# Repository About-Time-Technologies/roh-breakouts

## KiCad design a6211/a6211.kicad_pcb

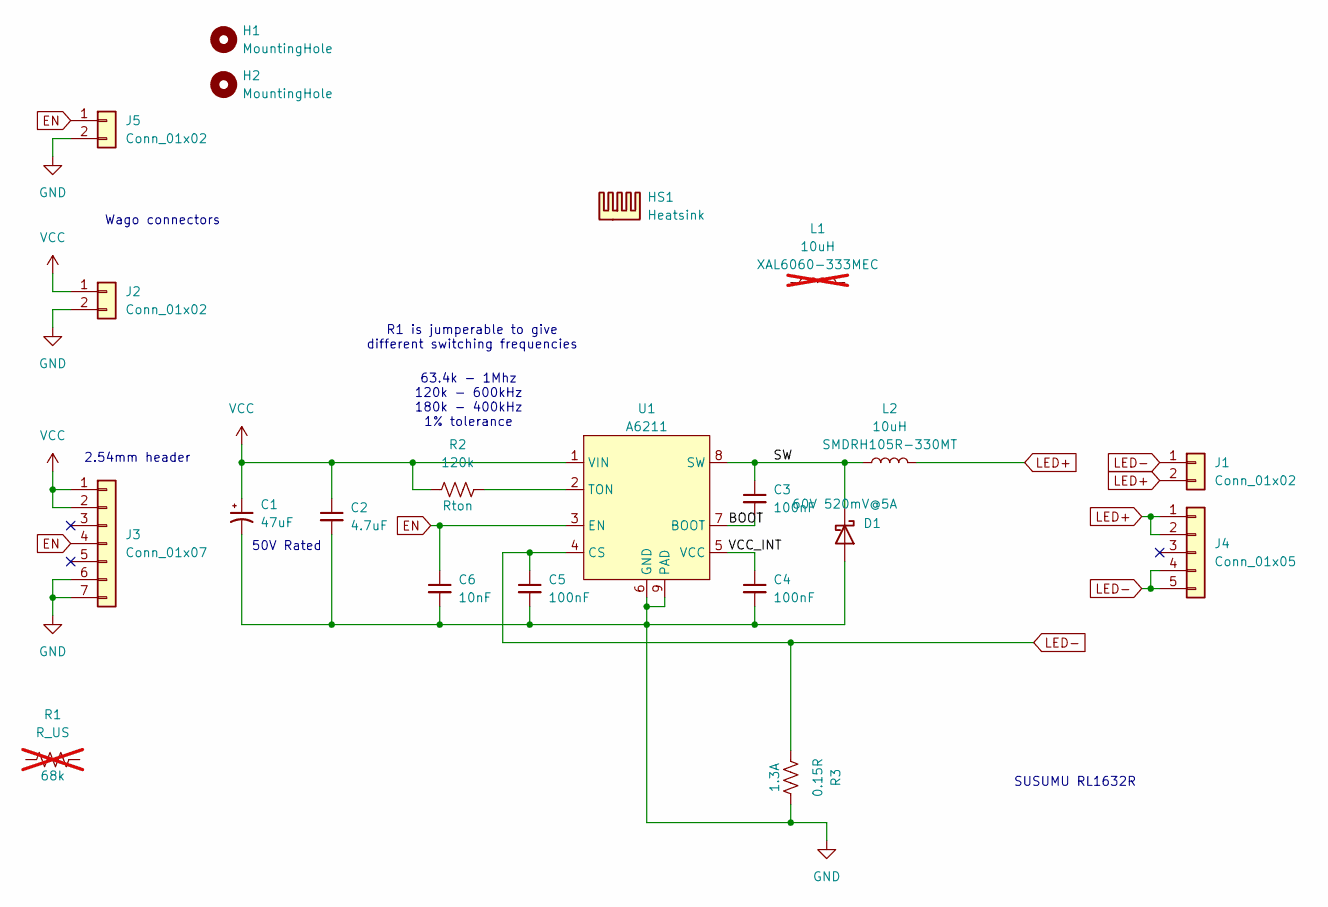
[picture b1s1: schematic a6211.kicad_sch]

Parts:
C1: 47uF; CP_Elec_8x10; LCSC C40078
C2: 4.7uF; C_1206_3216Metric; LCSC C29823
C3, C4, C5: 100nF; C_0603_1608Metric; LCSC C14663
C6: 10nF; C_0603_1608Metric; LCSC C57112
D1: D_Schottky; D_SMC; LCSC C7436542
H1, H2: MountingHole; MountingHole_3.2mm_M3
HS1: Heatsink; HSB02-101007
J1, J2: Conn_01x02; 2060-452-998-404 Wago
J3: Conn_01x07; PinHeader_1x07_P2.54mm_Vertical
J4: Conn_01x05; PinHeader_1x05_P2.54mm_Vertical
J5: Conn_01x02; PinHeader_1x02_P2.54mm_Vertical
L1: 10uH; L_Coilcraft_XAL6060-XXX; LCSC C5119929; not fitted
L2: 10uH; L_10.4x10.4_H4.8; LCSC C9186
R1: R_US; R_0603_1608Metric_Pad0.98x0.95mm_HandSolder; LCSC C23231; not fitted
R2: 120k; R_0603_1608Metric_Pad0.98x0.95mm_HandSolder; LCSC C25808
R3: 0.15R; R_1206_3216Metric; LCSC C2683383
U1: A6211; SOIC-8-1EP_3.9x4.9mm_P1.27mm_EP2.41x3.3mm_ThermalVias; LCSC C150827

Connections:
/BOOT: C3.2, U1.7 (BOOT)
/SW: C3.1, D1.1 (K), L2.1, U1.8 (SW)
/VCC_INT: C4.1, U1.5 (VCC)
EN: C6.1, J3.4, J5.1, U1.3 (EN)
GND: C1.2, C2.2, C4.2, C5.2, C6.2, D1.2 (A), J2.2, J3.6, J3.7, J5.2, R3.2, U1.6 (GND), U1.9 (PAD)
LED+: J1.2, J4.1, J4.2, L2.2
LED-: C5.1, J1.1, J4.4, J4.5, R3.1, U1.4 (CS)
unnamed: R2.2, U1.2 (TON)
VCC: C1.1, C2.1, J2.1, J3.1, J3.2, R2.1, U1.1 (VIN)

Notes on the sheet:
63.4k - 1Mhz 120k - 600kHz 180k - 400kHz 1% tolerance
SUSUMU RL1632R
2.54mm header
R1 is jumperable to give different switching frequencies
Wago connectors
50V Rated

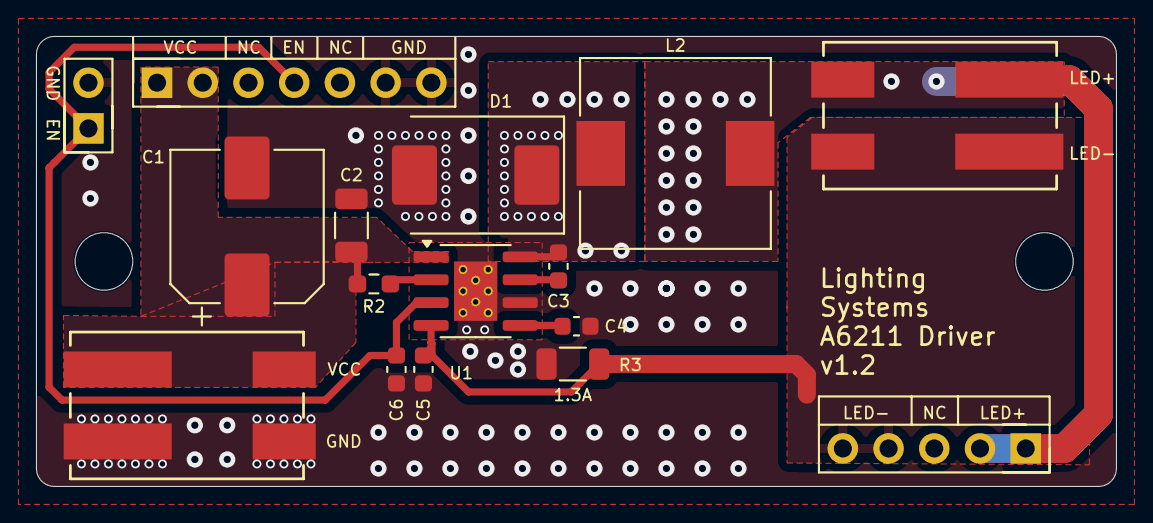
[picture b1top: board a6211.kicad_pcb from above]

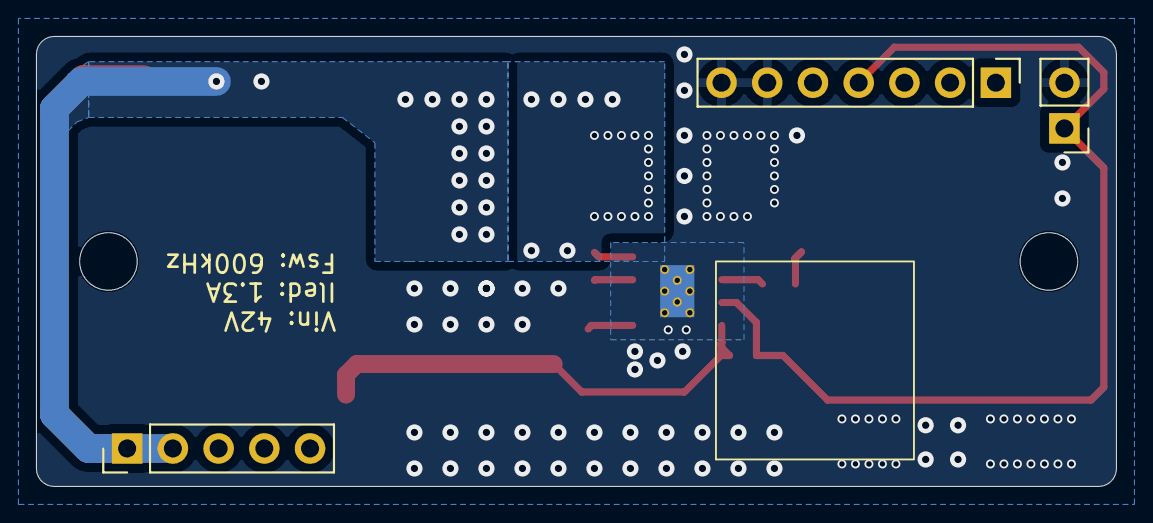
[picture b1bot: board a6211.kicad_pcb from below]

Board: 2 copper layers, 60.0 x 25.0 mm, 19 parts (4 on the bottom side), 9 nets.

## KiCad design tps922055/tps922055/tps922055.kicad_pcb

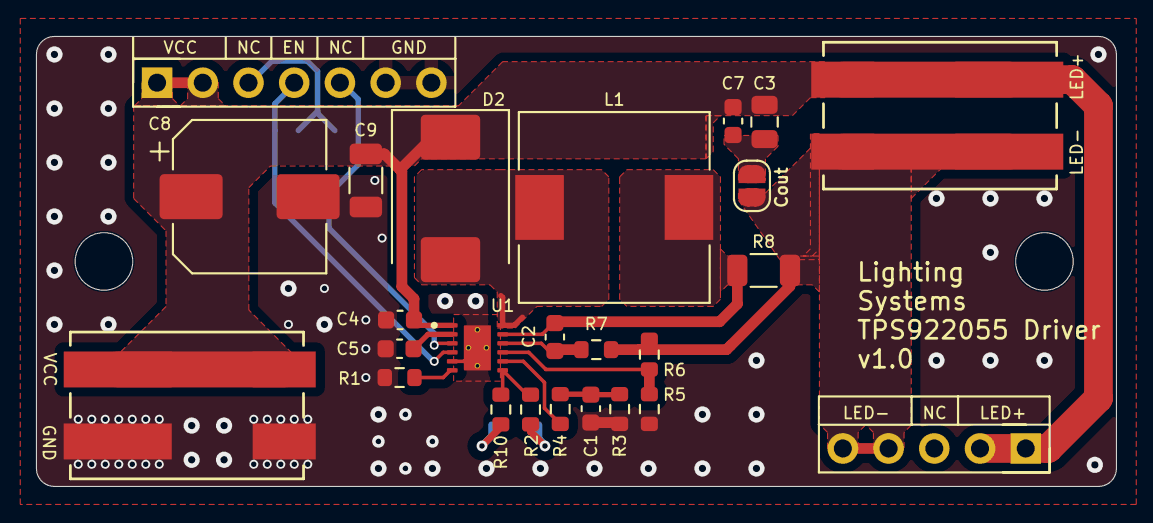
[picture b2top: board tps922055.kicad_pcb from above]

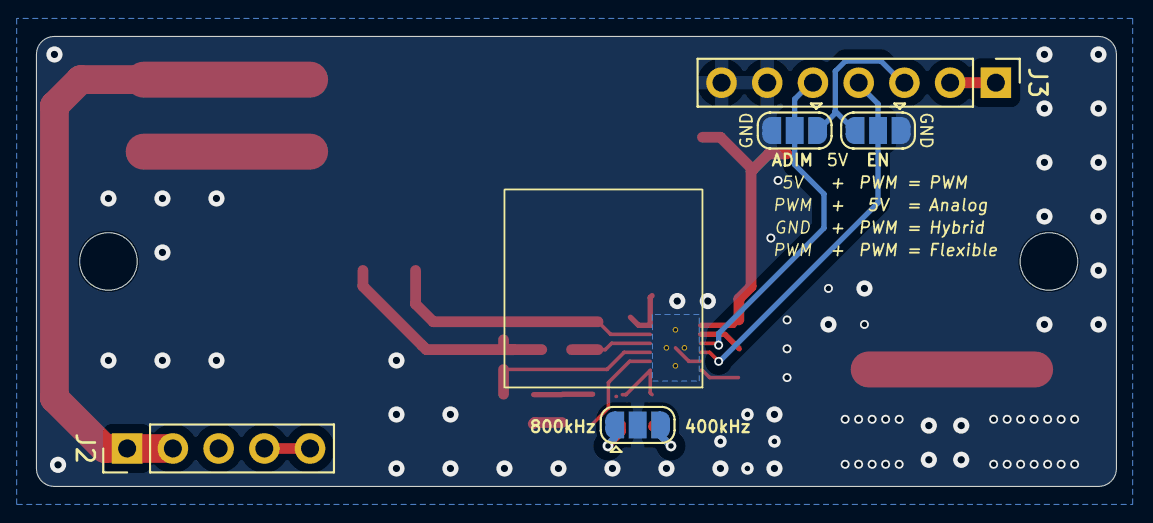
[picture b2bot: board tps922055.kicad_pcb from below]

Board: 2 copper layers, 60.0 x 25.0 mm, 31 parts (6 on the bottom side), 18 nets.

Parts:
C1, C2: 1nF; C_0603_1608Metric
C3: 1uF; C_0805_2012Metric
C4, C7: 100nF; C_0603_1608Metric
C5: 1uF; C_0603_1608Metric
C8: 47uF; CP_Elec_8x10
C9: 4.7uF; C_1206_3216Metric
D2: D_Schottky; D_SMC
H1, H2: MountingHole; MountingHole_3.2mm_M3
HS1: Heatsink; HSB02-101007
J1, J4: Conn_01x02; 2060-452-998-404 Wago
J2: Conn_01x05; PinHeader_1x05_P2.54mm_Vertical
J3: Conn_01x07; PinHeader_1x07_P2.54mm_Vertical
JP1, JP2, JP5: Jumper_3_Open; SolderJumper-3_P1.3mm_Open_RoundedPad1.0x1.5mm
JP3: Jumper_2_Open; SolderJumper-2_P1.3mm_Open_RoundedPad1.0x1.5mm
L1: 22uH; L_10.4x10.4_H4.8
R1, R2: 27k; R_0603_1608Metric
R3, R5, R6: 1M0; R_0603_1608Metric
R4, R7: 100R; R_0603_1608Metric
R8: 0.15R; R_1206_3216Metric
R10: 56k; R_0603_1608Metric
U1: TPS922052DRRR; SON50P300X300X100-13N

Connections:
5V: J3.3, JP1.3 (B), JP2.1 (A)
/COMP: R4.1, U1.8 (COMP)
/COMP2: C1.1, R3.1, R4.2
/CSN: C2.1, L1.2, R8.1, U1.11 (CSN)
/CSP: C2.2, R7.1, U1.10 (CSP)
/FSET: R2.1, R10.1, U1.7 (FSET)
/OUTCAP: C3.2, C7.2, JP3.2 (B)
/SW: D2.2 (A), L1.1, U1.12 (SW)
/TEMP: R1.1, U1.6 (TEMP)
/UVP: R5.1, R6.2, U1.9 (UVP)
/VCC: C5.2, U1.2 (VCC)
ADIM: J3.5, JP2.2 (C), U1.3 (ADIM/HD)
EN: J3.4, JP1.2 (C), U1.4 (EN/PWM)
GND: C1.2, C4.2, C5.1, C8.2, C9.2, J3.6, J3.7, J4.2, JP1.1 (A), JP2.3 (B), JP5.2 (C), R1.2, R3.2, R5.2, U1.5 (FAULT), U1.13 (GND), U1.14 (PAD), U1.15 (PAD), U1.16 (PAD), U1.17 (PAD)
LED+: C3.1, C4.1, C7.1, C8.1, C9.1, D2.1 (K), J1.2, J2.1, J2.2, J3.1, J3.2, J4.1, U1.1 (VIN)
LED-: J1.1, J2.4, J2.5, JP3.1 (A), R6.1, R7.2, R8.2
unnamed: JP5.1 (A), R2.2
unnamed: JP5.3 (B), R10.2

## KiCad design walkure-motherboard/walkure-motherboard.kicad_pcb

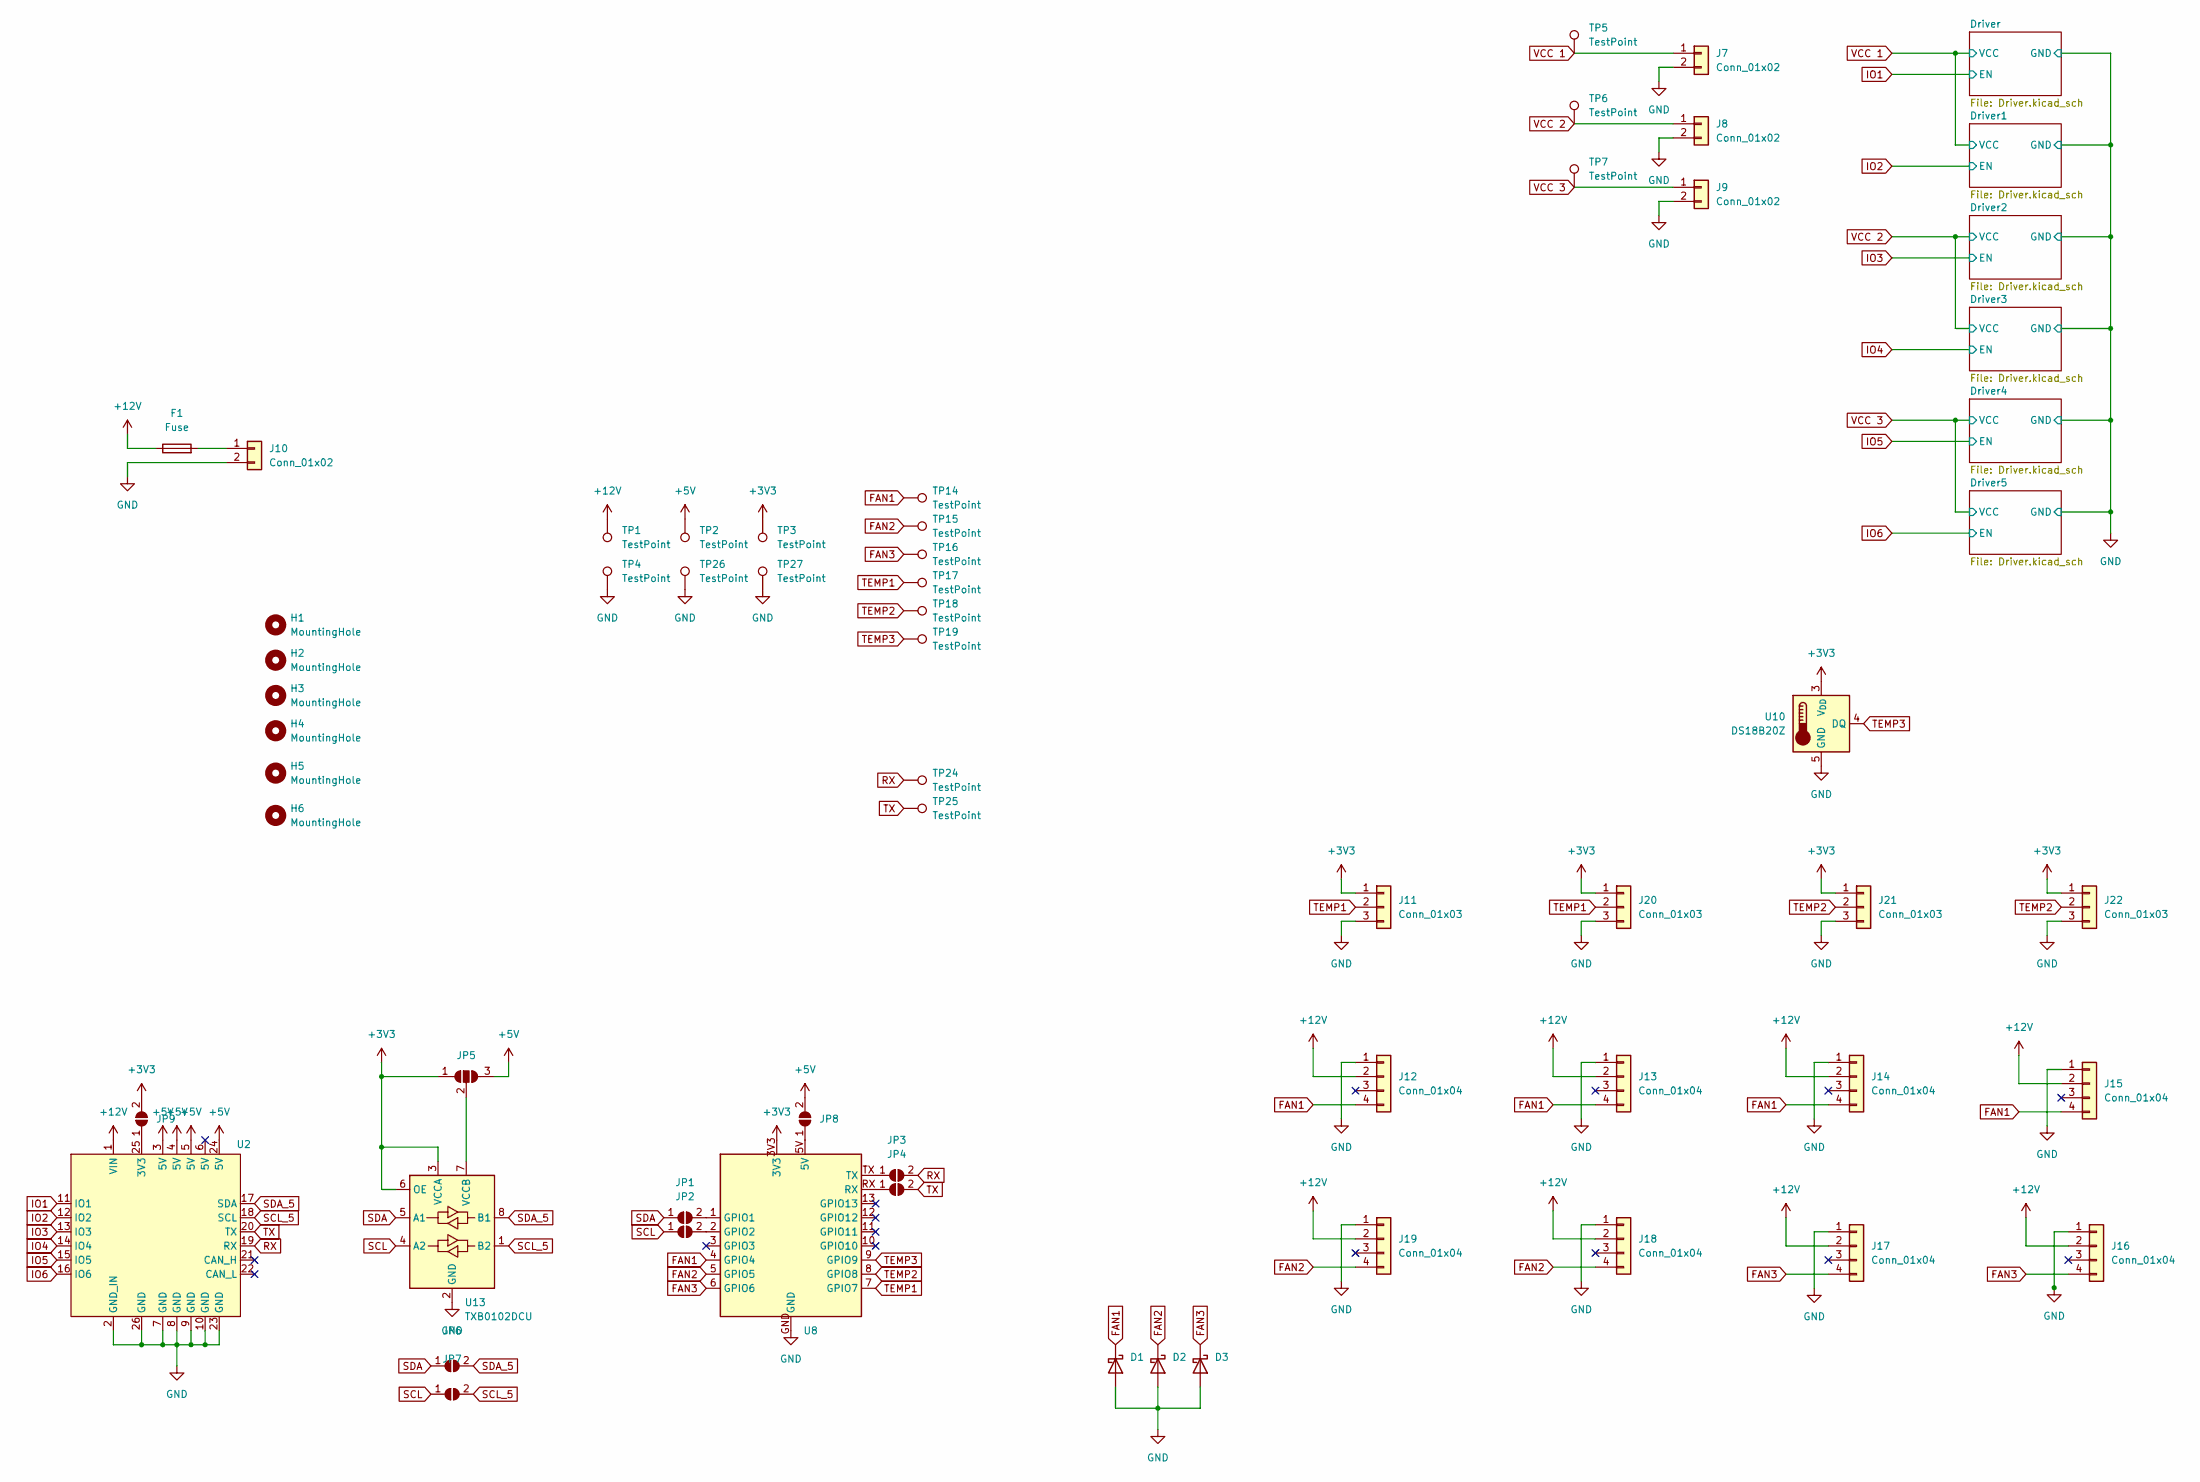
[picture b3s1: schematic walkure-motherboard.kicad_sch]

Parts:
D1, D2, D3: D_Schottky; D_DO-41_SOD81_P5.08mm_Vertical_AnodeUp
F1: Fuse; Keystone 4628
H1, H2, H3, H4, H5, H6: MountingHole; MountingHole_3.2mm_M3_ISO14580
J7, J8, J9, J10: Conn_01x02; 2060-452-998-404 Wago
J11, J20, J21, J22: Conn_01x03; PinHeader_1x03_P2.54mm_Vertical
J12, J13, J14, J15, J16, J17, J18, J19: Conn_01x04; PinHeader_1x04_P2.54mm_Vertical
JP1, JP2, JP3, JP4, JP6, JP7, JP8, JP9: SolderJumper_2_Open; SolderJumper-2_P1.3mm_Open_RoundedPad1.0x1.5mm
JP5: SolderJumper_3_Open; SolderJumper-3_P1.3mm_Open_RoundedPad1.0x1.5mm
TP1, TP2, TP3, TP4, TP5, TP6, TP7, TP14, TP15, TP16, TP17, TP18, TP19, TP24, TP25, TP26, TP27: TestPoint; TestPoint_Pad_D2.0mm
U2: MHCI-DMX
U8: ESP-32-S3-Zero - PTH
U10: DS18B20Z; SOIC-8_3.9x4.9mm_P1.27mm
U13: TXB0102DCU; VSSOP-8_2.3x2mm_P0.5mm; LCSC C60709

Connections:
+3V3: J11.1, J20.1, J21.1, J22.1, JP5.1 (A), JP9.2 (B), TP3.1, U8.3V3, U10.3 (V_{DD}), U13.3 (VCCA), U13.6 (OE)
+5V: JP5.3 (B), JP8.2 (B), TP2.1, U2.3 (5V), U2.4 (5V), U2.5 (5V), U2.24 (5V)
+12V: F1.1, J12.2, J13.2, J14.2, J15.2, J16.2, J17.2, J18.2, J19.2, TP1.1, U2.1 (VIN)
FAN1: D1.1 (K), J12.4, J13.4, J14.4, J15.4, TP14.1, U8.4 (GPIO4)
FAN2: D2.1 (K), J18.4, J19.4, TP15.1, U8.5 (GPIO5)
FAN3: D3.1 (K), J16.4, J17.4, TP16.1, U8.6 (GPIO6)
GND: D1.2 (A), D2.2 (A), D3.2 (A), J7.2, J8.2, J9.2, J10.2, J11.3, J12.1, J13.1, J14.1, J15.1, J16.1, J17.1, J18.1, J19.1, J20.3, J21.3, J22.3, TP4.1, TP26.1, TP27.1, U2.2 (GND_IN), U2.7 (GND), U2.8 (GND), U2.9 (GND), U2.10 (GND), U2.23 (GND), U2.26 (GND), U8.GND, U10.5 (GND), U13.2 (GND); also elsewhere on the board
IO1: U2.11 (IO1); also elsewhere on the board
IO2: U2.12 (IO2); also elsewhere on the board
IO3: U2.13 (IO3); also elsewhere on the board
IO4: U2.14 (IO4); also elsewhere on the board
IO5: U2.15 (IO5); also elsewhere on the board
IO6: U2.16 (IO6); also elsewhere on the board
unnamed: F1.2, J10.1
unnamed: JP1.2 (B), U8.1 (GPIO1)
unnamed: JP2.2 (B), U8.2 (GPIO2)
unnamed: JP3.1 (A), U8.TX
unnamed: JP4.1 (A), U8.RX
unnamed: JP5.2 (C), U13.7 (VCCB)
unnamed: JP8.1 (A), U8.5V
unnamed: JP9.1 (A), U2.25 (3V3)
RX: JP3.2 (B), TP24.1, U2.19 (RX)
SCL: JP2.1 (A), JP7.1 (A), U13.4 (A2)
SCL_5: JP7.2 (B), U2.18 (SCL), U13.1 (B2)
SDA: JP1.1 (A), JP6.1 (A), U13.5 (A1)
SDA_5: JP6.2 (B), U2.17 (SDA), U13.8 (B1)
TEMP1: J11.2, J20.2, TP17.1, U8.7 (GPIO7)
TEMP2: J21.2, J22.2, TP18.1, U8.8 (GPIO8)
TEMP3: TP19.1, U8.9 (GPIO9), U10.4 (DQ)
TX: JP4.2 (B), TP25.1, U2.20 (TX)
VCC 1: J7.1, TP5.1; also elsewhere on the board
VCC 2: J8.1, TP6.1; also elsewhere on the board
VCC 3: J9.1, TP7.1; also elsewhere on the board

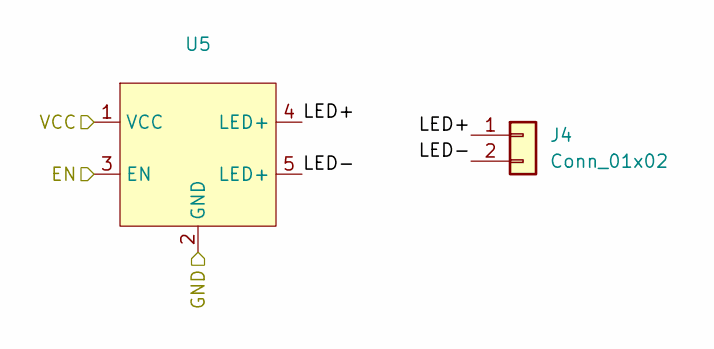
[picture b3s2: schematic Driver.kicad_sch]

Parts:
J4: Conn_01x02; 2060-452-998-404 Wago
U5: MHCI-A6211

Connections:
/Driver3/LED+: J4.1, U5.4 (LED+)
/Driver3/LED-: J4.2, U5.5 (LED+)
GND: U5.2 (GND); also elsewhere on the board
IO4: U5.3 (EN); also elsewhere on the board
VCC 2: U5.1 (VCC); also elsewhere on the board

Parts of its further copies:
J1, J2, J3, J5, J6: Conn_01x02; 2060-452-998-404 Wago
U1, U3, U4, U6, U7: MHCI-A6211

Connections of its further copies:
/Driver1/LED+: J1.1, U3.4 (LED+)
/Driver1/LED-: J1.2, U3.5 (LED+)
/Driver2/LED+: J3.1, U4.4 (LED+)
/Driver2/LED-: J3.2, U4.5 (LED+)
/Driver4/LED+: J5.1, U6.4 (LED+)
/Driver4/LED-: J5.2, U6.5 (LED+)
/Driver5/LED+: J6.1, U7.4 (LED+)
/Driver5/LED-: J6.2, U7.5 (LED+)
/Driver/LED+: J2.1, U1.4 (LED+)
/Driver/LED-: J2.2, U1.5 (LED+)
GND: U1.2 (GND), U3.2 (GND), U4.2 (GND), U6.2 (GND), U7.2 (GND); also elsewhere on the board
IO1: U1.3 (EN); also elsewhere on the board
IO2: U3.3 (EN); also elsewhere on the board
IO3: U4.3 (EN); also elsewhere on the board
IO5: U6.3 (EN); also elsewhere on the board
IO6: U7.3 (EN); also elsewhere on the board
VCC 1: U1.1 (VCC), U3.1 (VCC); also elsewhere on the board
VCC 2: U4.1 (VCC); also elsewhere on the board
VCC 3: U6.1 (VCC), U7.1 (VCC); also elsewhere on the board

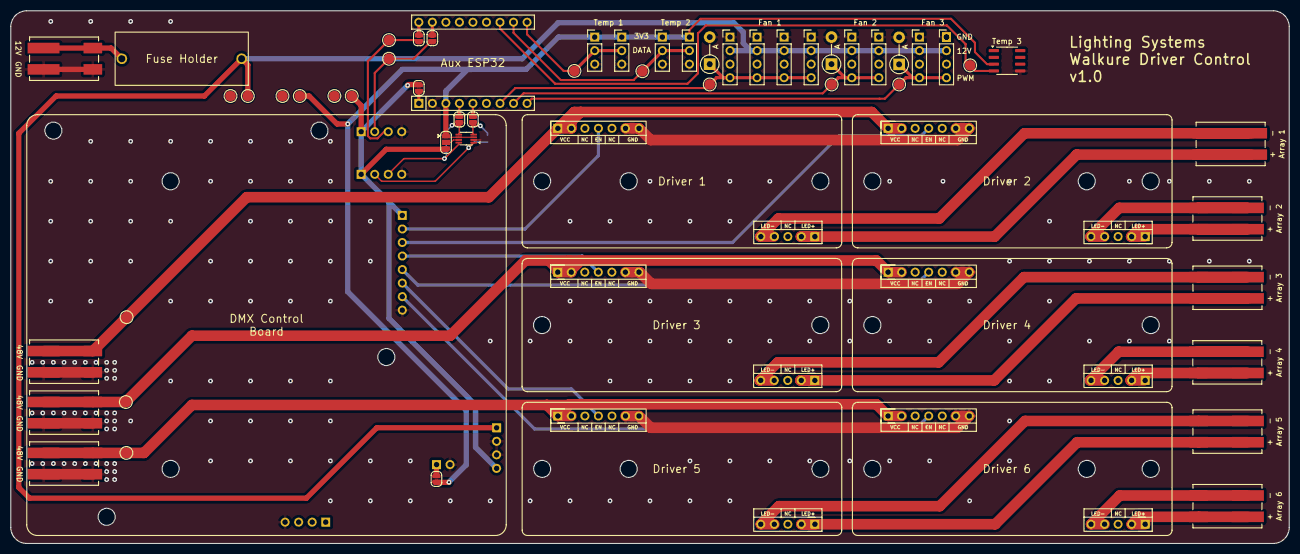
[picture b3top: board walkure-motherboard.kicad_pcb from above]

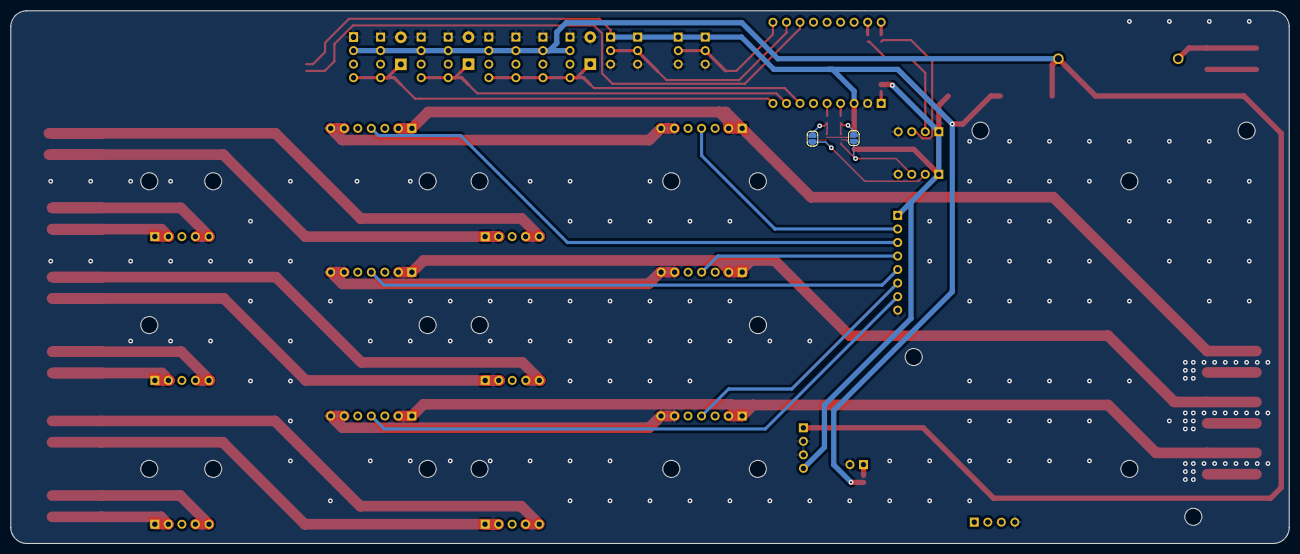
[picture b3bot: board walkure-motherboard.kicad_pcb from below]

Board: 2 copper layers, 240.0 x 100.0 mm, 68 parts (2 on the bottom side), 45 nets.

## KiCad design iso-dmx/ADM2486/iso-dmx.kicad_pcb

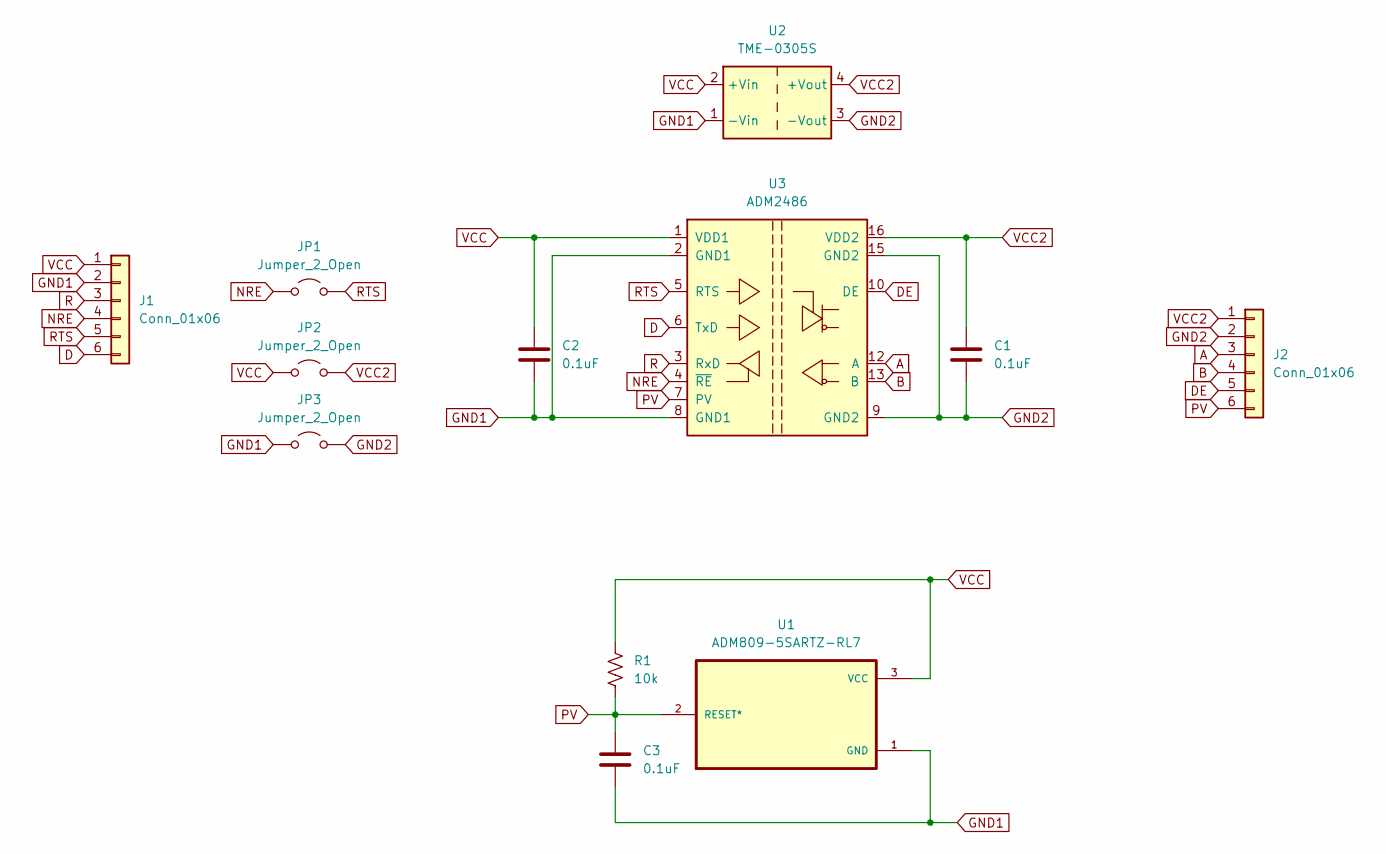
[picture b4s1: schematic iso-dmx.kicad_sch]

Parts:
C1, C2, C3: 0.1uF; C_1206_3216Metric_Pad1.33x1.80mm_HandSolder
J1, J2: Conn_01x06; PinHeader_1x06_P2.54mm_Vertical
JP1, JP2, JP3: Jumper_2_Open; SolderJumper-2_P1.3mm_Open_Pad1.0x1.5mm
R1: 10k; R_1206_3216Metric_Pad1.30x1.75mm_HandSolder
U1: ADM809-5SARTZ-RL7; SOT96P237X112-3N
U2: TME-0305S; Converter_DCDC_TRACO_TME_03xxS_05xxS_12xxS_Single_THT
U3: ADM2486; SOIC-16W_7.5x10.3mm_P1.27mm

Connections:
A: J2.3, U3.12 (A)
B: J2.4, U3.13 (B)
D: J1.6, U3.6 (TxD)
DE: J2.5, U3.10 (DE)
GND1: C2.2, C3.2, J1.2, JP3.1 (A), U1.1 (GND), U2.1 (-Vin), U3.2 (GND1), U3.8 (GND1)
GND2: C1.2, J2.2, JP3.2 (B), U2.3 (-Vout), U3.9 (GND2), U3.15 (GND2)
NRE: J1.4, JP1.1 (A), U3.4 (~RE)
PV: C3.1, J2.6, R1.2, U1.2 (RESET*), U3.7 (PV)
R: J1.3, U3.3 (RxD)
RTS: J1.5, JP1.2 (B), U3.5 (RTS)
VCC: C2.1, J1.1, JP2.1 (A), R1.1, U1.3 (VCC), U2.2 (+Vin), U3.1 (VDD1)
VCC2: C1.1, J2.1, JP2.2 (B), U2.4 (+Vout), U3.16 (VDD2)

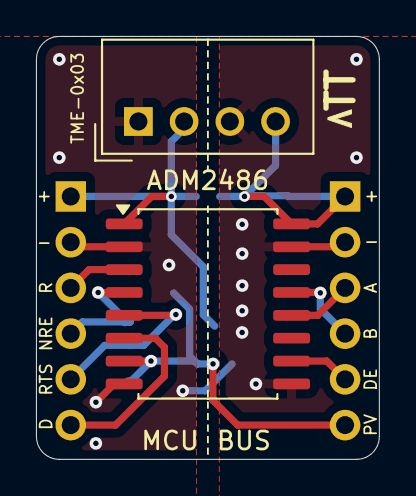
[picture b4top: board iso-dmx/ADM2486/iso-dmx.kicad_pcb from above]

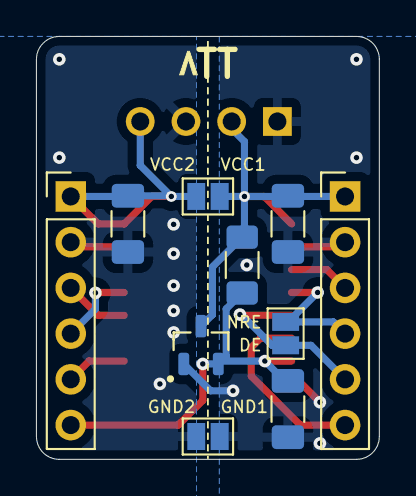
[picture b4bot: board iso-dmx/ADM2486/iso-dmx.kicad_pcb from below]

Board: 2 copper layers, 19.0 x 23.5 mm, 12 parts (10 on the bottom side), 12 nets.

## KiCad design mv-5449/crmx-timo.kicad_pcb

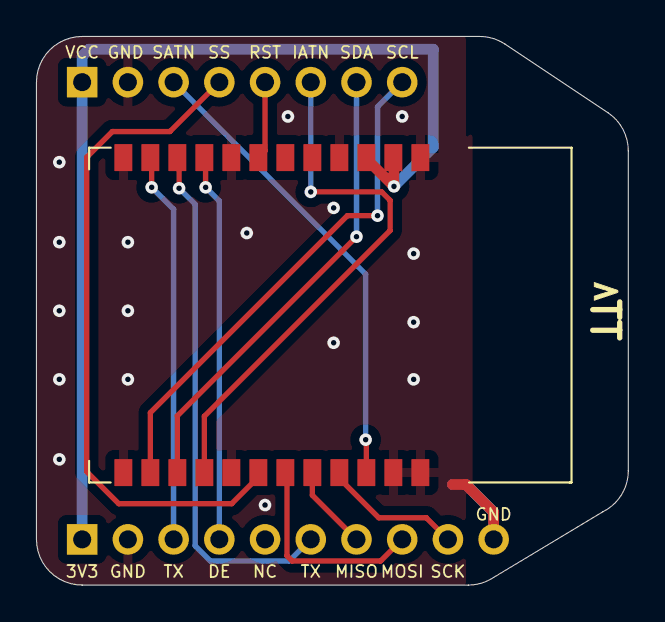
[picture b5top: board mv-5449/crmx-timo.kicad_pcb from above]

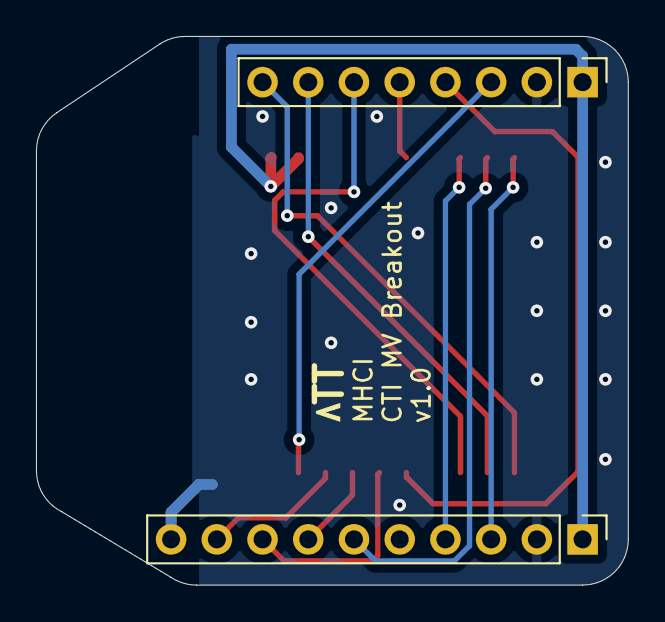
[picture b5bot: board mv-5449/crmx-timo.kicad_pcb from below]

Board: 2 copper layers, 32.9 x 30.5 mm, 3 parts (2 on the bottom side), 14 nets.

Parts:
J1: Conn_01x10; PinHeader_1x10_P2.54mm_Vertical
J2: Conn_01x08; PinHeader_1x08_P2.54mm_Vertical
U2: CTI-5994

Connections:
CTI_RESET: J2.5, U2.7 (nRESET)
DMX_DE: J1.4, U2.9 (UART_TXE)
DMX_RX: J1.6, U2.10 (UART_RX)
DMX_TX: J1.3, U2.11 (UART_TX)
GND: J1.2, J1.10, J2.2, U2.1 (GND), U2.4 (GND), U2.8 (GND), U2.12 (GND), U2.13 (GND), U2.17 (GND), U2.23 (GND), U2.24 (GND)
I2C_SCL: J2.8, U2.14 (I2C_SCL)
I2C_SDA: J2.7, U2.15 (I2C_SDA)
I2C_nATTN: J2.6, U2.16 (I2C_nATTN)
SPI_MISO: J1.7, U2.20 (SPI_MISO)
SPI_MOSI: J1.8, U2.19 (SPI_MOSI)
SPI_SCK: J1.9, U2.21 (SPI_CLK)
SPI_nATTN: J2.3, U2.22 (SPI_nATTN)
SPI_nSS: J2.4, U2.18 (SPI_nSS)
VCC: J1.1, J2.1, U2.2 (VCC), U2.3 (VCC)

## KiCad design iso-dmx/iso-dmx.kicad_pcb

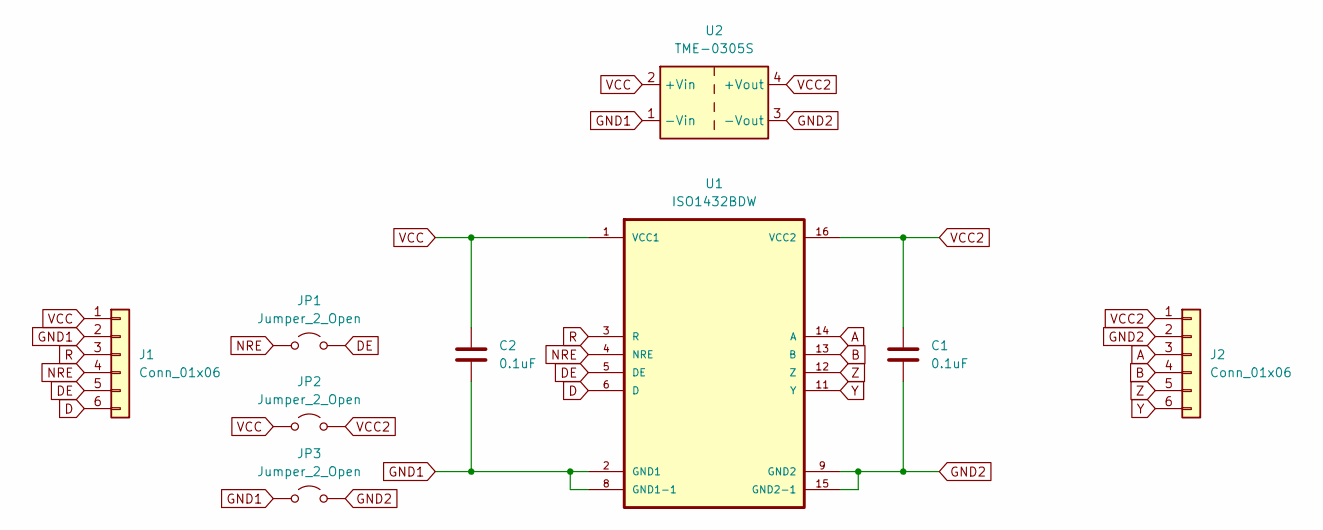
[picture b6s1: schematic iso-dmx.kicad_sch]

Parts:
C1, C2: 0.1uF; C_1206_3216Metric_Pad1.33x1.80mm_HandSolder
J1, J2: Conn_01x06; PinHeader_1x06_P2.54mm_Vertical
JP1, JP2, JP3: Jumper_2_Open; SolderJumper-2_P1.3mm_Open_Pad1.0x1.5mm
U1: ISO1432BDW; SOIC127P1030X265-16N
U2: TME-0305S; Converter_DCDC_TRACO_TME_03xxS_05xxS_12xxS_Single_THT

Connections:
A: J2.3, U1.14 (A)
B: J2.4, U1.13 (B)
D: J1.6, U1.6 (D)
DE: J1.5, JP1.2 (B), U1.5 (DE)
GND1: C2.2, J1.2, JP3.1 (A), U1.2 (GND1), U1.8 (GND1-1), U2.1 (-Vin)
GND2: C1.2, J2.2, JP3.2 (B), U1.9 (GND2), U1.15 (GND2-1), U2.3 (-Vout)
NRE: J1.4, JP1.1 (A), U1.4 (NRE)
R: J1.3, U1.3 (R)
VCC: C2.1, J1.1, JP2.1 (A), U1.1 (VCC1), U2.2 (+Vin)
VCC2: C1.1, J2.1, JP2.2 (B), U1.16 (VCC2), U2.4 (+Vout)
Y: J2.6, U1.11 (Y)
Z: J2.5, U1.12 (Z)

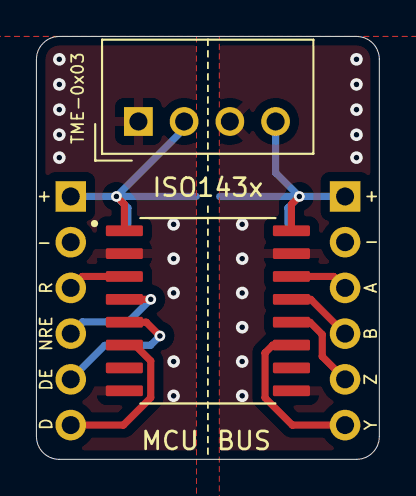
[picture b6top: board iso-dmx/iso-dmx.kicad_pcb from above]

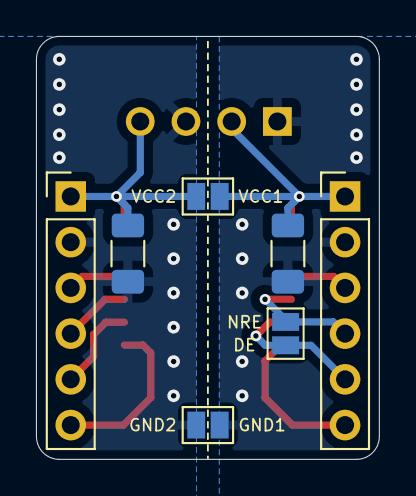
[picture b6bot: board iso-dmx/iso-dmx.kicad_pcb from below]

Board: 2 copper layers, 19.0 x 23.5 mm, 9 parts (7 on the bottom side), 12 nets.

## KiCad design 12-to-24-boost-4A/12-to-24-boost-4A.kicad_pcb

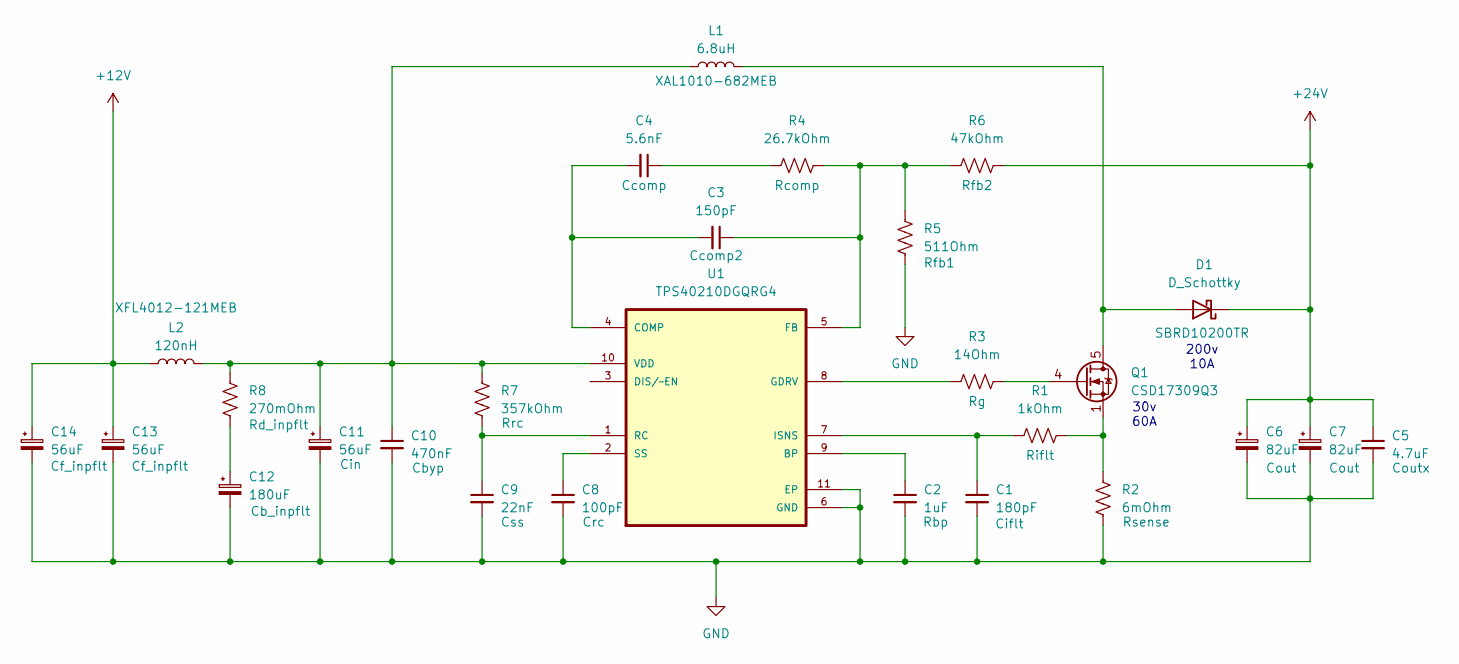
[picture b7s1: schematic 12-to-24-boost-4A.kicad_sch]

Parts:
C1: 180pF; C_0805_2012Metric
C2: 1uF; C_0603_1608Metric
C3: 150pF; C_0402_1005Metric
C4: 5.6nF; C_0805_2012Metric
C5: 4.7uF; C_0805_2012Metric
C6, C7: 82uF; CP_Elec_8x11.9
C8: 100pF; C_0805_2012Metric
C9: 22nF; C_0805_2012Metric
C10: 470nF; C_0805_2012Metric
C11: 56uF; CP_Elec_6.3x5.8
C12: 180uF; CP_Elec_8x6.9
C13, C14: 56uF; CP_Elec_5x5.9
D1: D_Schottky; TO-252-2
L1: 6.8uH; L_Coilcraft_XAL1010-XXX
L2: 120nH; L_Changjiang_FNR4012S
Q1: CSD17309Q3; TDSON-8-1
R1: 1kOhm; R_0402_1005Metric
R2: 6mOhm; R_0612_1632Metric
R3: 14Ohm; R_0402_1005Metric
R4: 26.7kOhm; R_0402_1005Metric
R5: 511Ohm; R_0402_1005Metric
R6: 47kOhm; R_0603_1608Metric_Pad0.98x0.95mm_HandSolder
R7: 357kOhm; C_0402_1005Metric
R8: 270mOhm; R_0603_1608Metric
U1: TPS40210DGQRG4; IC_XTR111AIDGQR

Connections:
+12V: C13.1, C14.1, L2.1
+24V: C5.1, C6.1, C7.1, D1.1 (K), R6.1
GND: C1.2, C2.2, C5.2, C6.2, C7.2, C8.2, C9.2, C10.2, C11.2, C12.2, C13.2, C14.2, R2.1, R5.1, U1.6 (GND), U1.11 (EP)
unnamed: C4.1, R4.1
unnamed: C12.1, R8.1
unnamed: D1.2 (A), L1.2, Q1.5 (D)
unnamed: Q1.4 (G), R3.2
unnamed: Q1.1 (S), Q1.2 (S), Q1.3 (S), R1.2, R2.2
unnamed: C2.1, U1.9 (BP)
unnamed: C3.2, C4.2, U1.4 (COMP)
unnamed: C3.1, R4.2, R5.2, R6.2, U1.5 (FB)
unnamed: R3.1, U1.8 (GDRV)
unnamed: C1.1, R1.1, U1.7 (ISNS)
unnamed: C9.1, R7.1, U1.1 (RC)
unnamed: C8.1, U1.2 (SS)
unnamed: C10.1, C11.1, L1.1, L2.2, R7.2, R8.2, U1.10 (VDD)

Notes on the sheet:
200v 10A
30v 60A

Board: 2 copper layers, 27 parts (0 on the bottom side), 16 nets, no tracks yet.

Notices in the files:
parts and their libraries:
Copyright 2016 Accelerated Designs. All rights reserved.
